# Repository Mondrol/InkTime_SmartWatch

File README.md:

# INK TIME SMARTWATCH

Un smartwatch bazat pe arhitectura **nRF52840**, echipat cu un ecran **e-Paper** pentru consum ultra-redus de energie și un sistem de alertă haptică.

---

## Cuprins

1. [Diagrama Bloc](#diagrama-bloc)
2. [Descrierea Funcționalității Hardware](#descrierea-funcționalității-hardware)
3. [Bill of Materials (BOM)](#bill-of-materials-bom)
4. [Configurația Pinilor nRF52840](#configurația-pinilor-nrf52840)

---

## Diagrama Bloc

```
┌─────────────────────────────────────────────────────────────┐
│                        POWER SUPPLY                         │
│                                                             │
│  Li-Po Battery (3.7V)                                       │
│       │                                                     │
│       ▼                                                     │
│  BQ25180 (Charger IC)  ◄──── USB Type-C                     │
│       │                                                     │
│       ▼                                                     │
│  RT6160A (Buck-Boost)  ──► 3.3V stable output              │
│       │                                                     │
│  MAX17048 (Fuel Gauge) ──► I2C ──► nRF52840                 │
└─────────────────────────────────────────────────────────────┘

┌─────────────────────────────────────────────────────────────┐
│                     PROCESSING UNIT                         │
│                                                             │
│              nRF52840 (ARM Cortex-M4F)                      │
│         ┌──────────────┴──────────────┐                     │
│         │                            │                      │
│       SPI bus                     I2C bus                   │
│         │                            │                      │
│   e-Paper Display              ┌─────┴──────┐               │
│   (1.54")                      │            │               │
│                            BMA423      DRV2605L              │
│                          (Accel.)    (Haptic Driver)         │
└─────────────────────────────────────────────────────────────┘
```

---

## Descrierea Funcționalității Hardware

Sistemul este construit în jurul SoC-ului **nRF52840**, optimizat pentru un consum ultra-scăzut de energie și securitate hardware.

### Microcontroller — nRF52840

Procesor ARM Cortex-M4F cu unitate de criptare hardware CryptoCell-310. Gestionează stack-ul **Bluetooth Low Energy (BLE)** și coordonează toate perifericele. Rulează la 64 MHz, dar stă majoritatea timpului în modul **System ON Sleep** (~3 µA).

### Sistemul de Alimentare (Power Tree)

| Componentă | Rol |
|---|---|
| **BQ25180** | IC de încărcare cu Power Path — permite încărcarea bateriei LiPo și alimentarea simultană a sistemului via USB Type-C |
| **MAX17048** | Fuel Gauge — măsoară precis starea de încărcare (SoC) și tensiunea bateriei, comunicând prin I2C |
| **RT6160A** | Regulator Buck-Boost — asigură o tensiune stabilă de 3.3V indiferent de nivelul de descărcare al bateriei |

### Afișaj e-Paper (1.54")

Display de tip *Electronic Ink* care consumă curent **doar la refresh**. Include un circuit de protecție cu un PFET (DMG2305UX) pentru a opri complet alimentarea ecranului în standby, eliminând scurgerile de curent. Comunică cu MCU prin **SPI** (interfață de mare viteză).

### Senzor de Mișcare — BMA423

Accelerometru triaxial de mică putere (12-bit, 3 axe). Utilizat pentru:
- **Pedometru** (numărarea pașilor)
- **Detectarea gesturilor** — ex: *tilt-to-wake* (ridicarea mâinii aprinde ecranul)

### Driver Haptic — DRV2605L

Controlează motorul de vibrații (ERM/LRA) folosind librării de efecte pre-programate pentru feedback tactil. Comunică prin **I2C**.

### Cristale de Referință

**Cristal 32 MHz (X1)** — esențial pentru funcționarea blocului radio (Bluetooth). Oferă referința de înaltă frecvență necesară stabilității semnalului RF și procesării rapide a datelor.

**Cristal 32.768 kHz (X2)** — componentă critică pentru optimizarea consumului. Permite funcționarea ceasului de timp real (RTC) în modurile de **Deep Sleep**, menținând precizia timpului cu un consum infim de energie, fără a fi nevoie de oscilatorul intern RC (mai puțin precis și mai consumator).

### Antena 2.4 GHz

Antenă de tip **SMD ceramic** (Johanson 2450AT18B100E) pentru frecvența de 2.4 GHz (BLE). A fost respectată o zonă de *keep-out* (fără cupru) pe toate straturile sub antenă pentru a preveni atenuarea semnalului.

### Interfețe de Comunicație

| Interfață | Periferice conectate |
|---|---|
| **I2C** | BMA423, DRV2605L, BQ25180, MAX17048 |
| **SPI** | Display e-Paper (interfață de mare viteză) |
| **GPIO cu întreruperi** | Butoane UP / ENTER / DOWN |
| **SWD** | Programare și debugging via Tag-Connect (J2) |

### Consumul de Energie

Bateria de **250 mAh** susține o autonomie estimată de **30–45 zile**, datorită:
- Ecranului e-Paper care nu consumă energie între actualizări
- Senzorilor configurați pe modul de consum minim cu întreruperi
- nRF52840 în System ON Sleep (~3 µA) marea majoritate a timpului

---

## Bill of Materials (BOM)

| Componentă | Descriere | Qty | Ref. Designator | Producător |
|---|---|:---:|---|---|
| **nRF52840** | MCU ARM Cortex-M4F + BLE 5.0 | 1 | U1 | Nordic Semiconductor |
| **BQ25180YBGR** | IC Încărcare Baterie Li-Po/Li-Ion | 1 | IC1 | Texas Instruments |
| **MAX17048G+T10** | Fuel Gauge 1-Cell cu ModelGauge | 1 | U2 | Analog Devices (Maxim) |
| **RT6160AWSC** | Regulator Buck-Boost DC-DC I2C | 1 | IC9 | Richtek |
| **DRV2605YZFR** | Driver Haptic ERM/LRA | 1 | IC2 | Texas Instruments |
| **BMA423** | Accelerometru Triaxial Low-g 12-bit | 1 | IC3 | Bosch Sensortec |
| **2450AT18B100E** | Antenă SMD 2.45 GHz (BLE) | 1 | ANT1 | Johanson Technology |
| **KH-TYPE-C-16P** | Conector USB Type-C 16 pini | 1 | J4 | Kinghelm |
| **503480-2400** | Conector FPC 24 pini, pitch 0.5mm (Display) | 1 | J1 | Molex |
| **TC2030-IDC** | Conector programare Tag-Connect 6 pini | 1 | J2 | Tag-Connect |
| **USBLC6-2SC6Y** | Diodă TVS Protecție ESD (USB) | 1 | D3 | STMicroelectronics |
| **MBR0530** | Diodă Schottky 30V / 0.5A | 3 | D2, D4, D5 | ON Semiconductor |
| **DMG2305UX-7** | MOSFET P-Channel 20V / 4.2A (e-Paper power switch) | 1 | Q1 | Diodes Inc. |
| **SI1308EDL-T1-GE3** | MOSFET N-Channel 30V / 1.5A | 1 | Q3 | Vishay Siliconix |
| **EVP-AKE31A** | Butoane Tactile SMD (Navigare) | 3 | SW_UP, SW_DN, SW_ENT | Panasonic |
| **744043680** | Inductor / Bobină 68 µH | 1 | L5 | Würth Elektronik |
| **FTC252012SR47MBCA** | Inductor SMD 0.47 µH | 1 | L7 | TDK |
| **Cristal 32 MHz** | Referință RF pentru bloc radio BLE | 1 | X1 | — |
| **Cristal 32.768 kHz** | Referință RTC pentru Deep Sleep | 1 | X2 | — |
| **Condensatori / Rezistențe** | Pasive SMD (0201, 0402) | ~60 | C*, R* | — |
| **Test Pads** | Puncte de test (3.3V, GND, SWD, I2C etc.) | 14 | TP_* | — |

---

## Configurația Pinilor nRF52840

### Interfața Ecranului e-Paper (SPI)

| Semnal | Pin nRF52 | Direcție | Descriere |
|---|---|---|---|
| EPD_SCK | P0.28 | Output | Clock SPI pentru refresh ecran |
| EPD_MOSI | P0.29 | Output | Date imagine (frame buffer) |
| EPD_CS | P0.30 | Output | Chip Select — activează comunicația cu display-ul |
| EPD_DC | P0.31 | Output | Data/Command — diferențiază comenzile de datele de imagine |
| EPD_BUSY | P0.04 | Input | Semnal activ cât timp ecranul procesează un refresh |
| EPD_PWR | P0.13 | Output | Enable alimentare ecran — dezactivat complet în standby |

### Magistrala Senzorilor (I2C)

Toți senzorii (BMA423, MAX17048, DRV2605L, BQ25180) împart aceeași magistrală I2C.

| Semnal | Pin nRF52 | Descriere |
|---|---|---|
| I2C_SDA | P0.26 | Linie de date (partajată între toți senzorii) |
| I2C_SCL | P0.27 | Linie de clock |

### Butoane de Navigare

Pini configurați cu pull-up intern și capabili de **wake-up din Deep Sleep** prin întrerupere hardware.

| Buton | Pin nRF52 | Funcție |
|---|---|---|
| UP | P1.00 | Navigare meniu — sus |
| DOWN | P1.01 | Navigare meniu — jos |
| ENTER | P1.02 | Selecție / Confirmare |

### Alte Conexiuni Importante

| Semnal | Pin nRF52 | Descriere |
|---|---|---|
| SHAKER_EN | P0.02 | PWM / Enable pentru driver haptic DRV2605 |
| GAUGE_INT | P1.15 | Întrerupere de la MAX17048 la nivel critic de baterie |
| LED_1 | P0.13 | LED de stare pentru notificări vizuale |
| LED_2 | P0.14 | LED de stare secundar |
| SWDIO | — | Programare și debug via Tag-Connect J2 |
| SWDCLK | — | Clock SWD pentru J-Link |

---

## Imagini PCB

| PCB 3D View | Exploded View | Final View |
|---|---|---|
| `./Images/PCB_3D.png` | `./Images/exploded_view.png` | `./Images/final_view.png` |

---

*INK TIME SMARTWATCH — Hardware Design Documentation*

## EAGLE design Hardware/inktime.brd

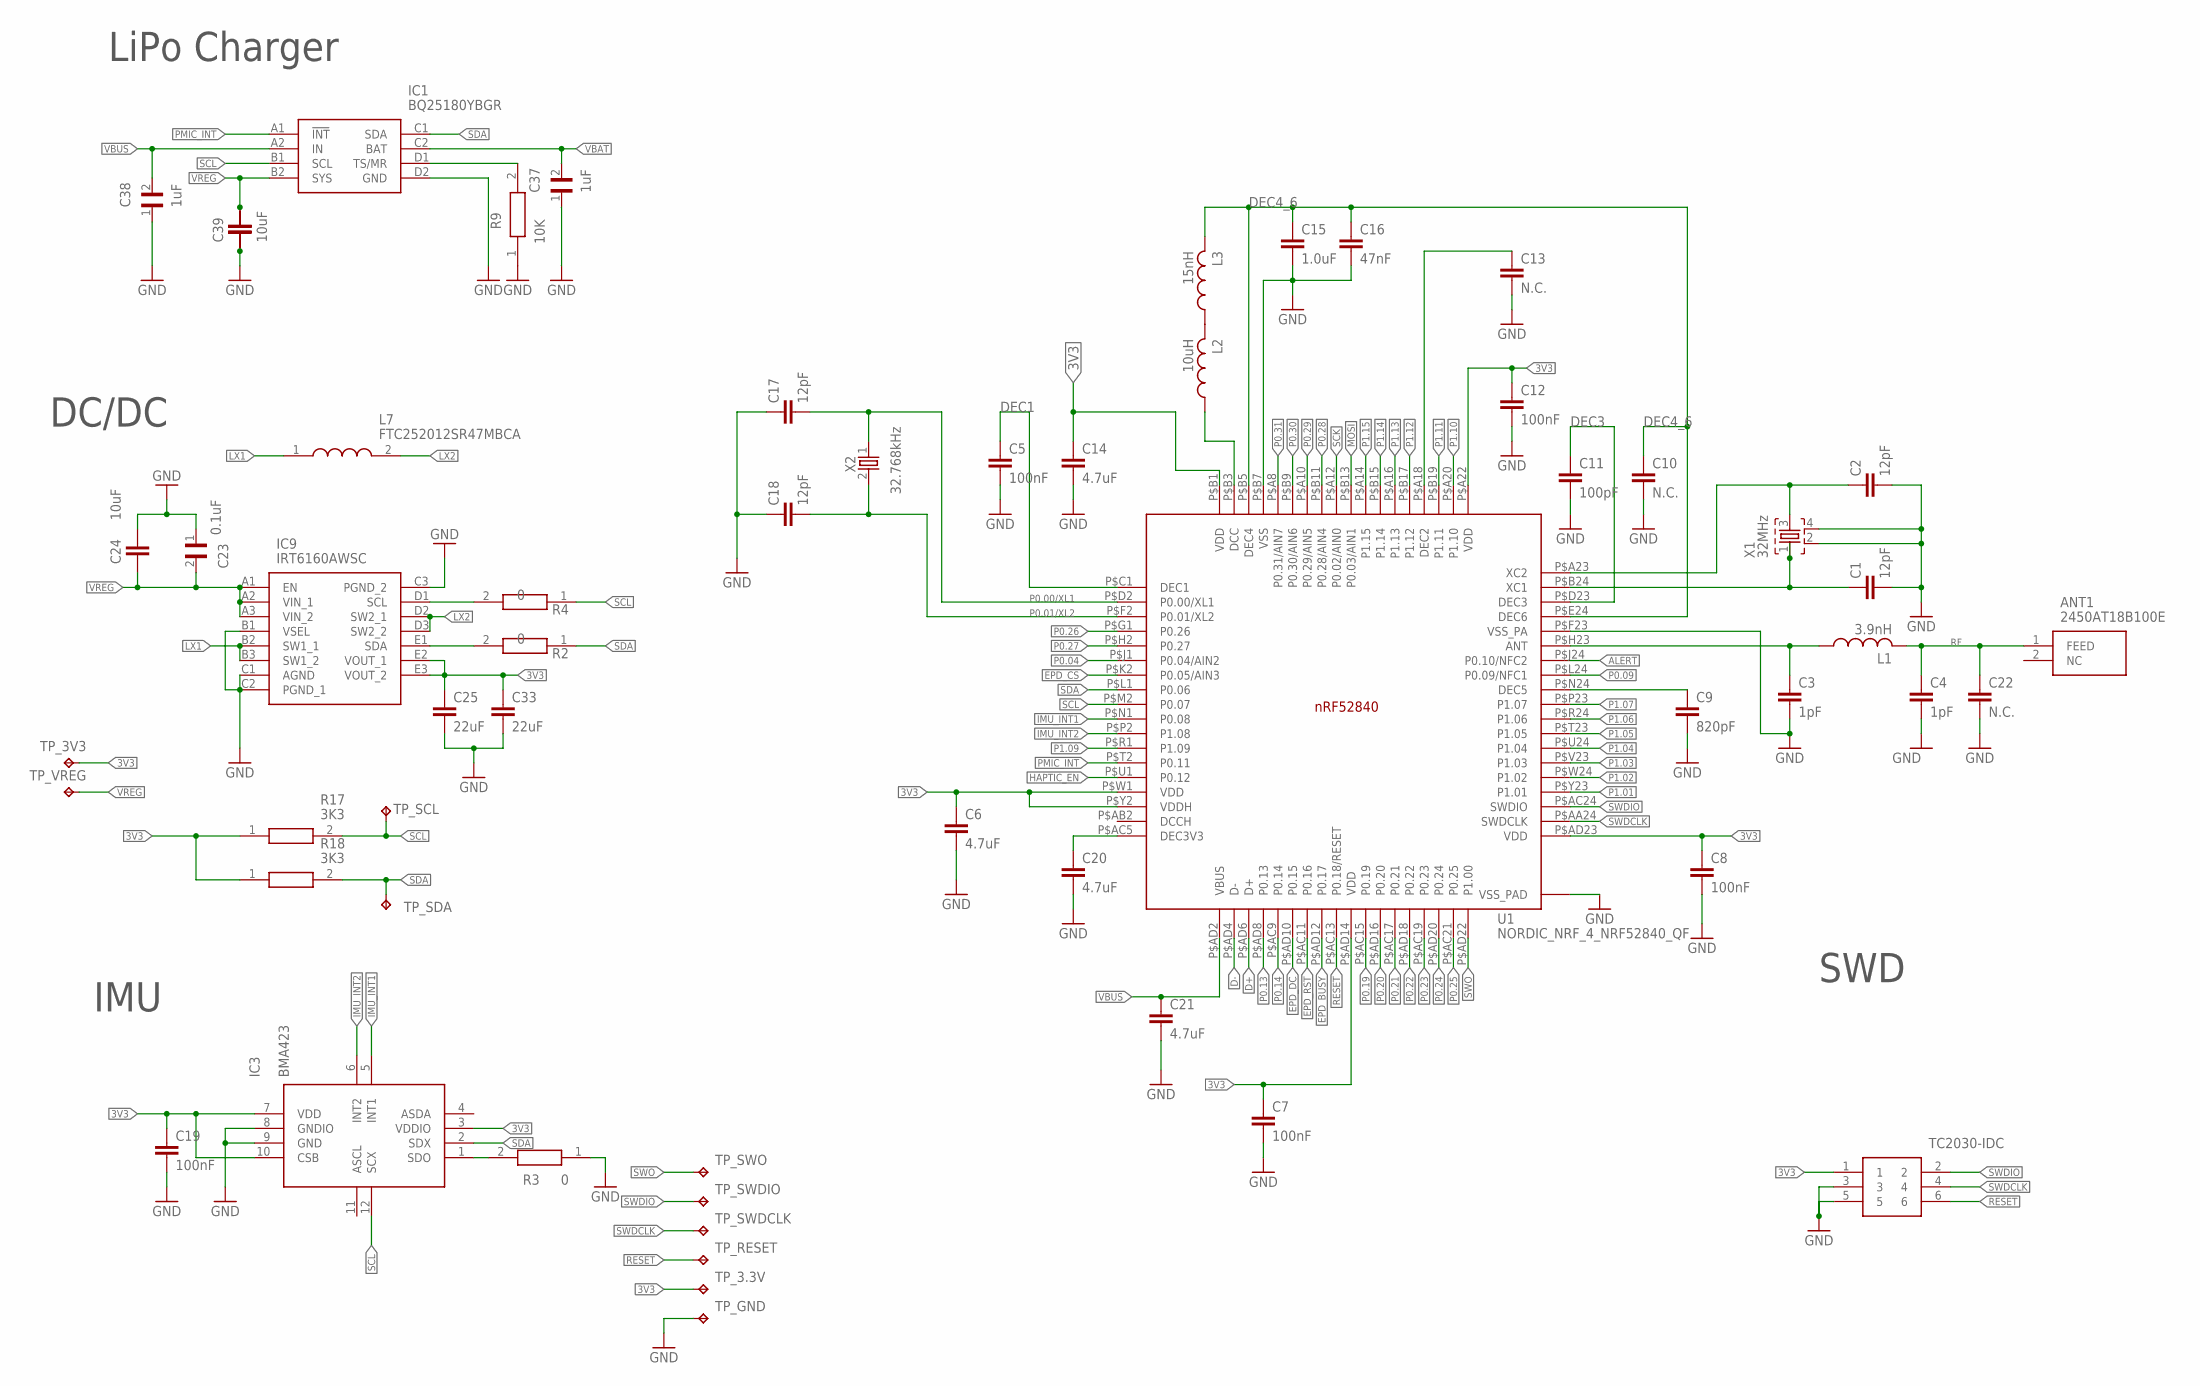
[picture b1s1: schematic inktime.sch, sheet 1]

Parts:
ANT1: 2450AT18B100E; 2450AT18B100E_ANTC3216X140N
C1, C2, C17, C18: 12pF; NORDIC_NRF_3_RESC0201_L
C3, C4: 1pF; NORDIC_NRF_3_RESC0201_L
C5, C7, C8, C12, C19: 100nF; NORDIC_NRF_3_RESC0201_L
C6, C14, C20, C21: 4.7uF; NORDIC_NRF_3_RESC0402_L
C9: 820pF; NORDIC_NRF_3_RESC0201_L
C10, C13, C22: N.C.; NORDIC_NRF_3_RESC0201_L
C11: 100pF; NORDIC_NRF_3_RESC0201_L
C15: 1.0uF; NORDIC_NRF_3_RESC0402_L
C16: 47nF; NORDIC_NRF_3_RESC0201_L
C23: 0.1uF; GRM011R60J152KE01L_2_CAPC0201X13N
C24, C39: 10uF; NORDIC_NRF_3_RESC0402_L
C25, C33: 22uF; NORDIC_NRF_3_RESC0402_L
C37, C38: 1uF; GRM011R60J152KE01L_2_CAPC0201X13N
IC1: BQ25180YBGR; BQ25180YBGR_BGA8C40P2X4_100X155X50
IC3: BMA423; BMA423_BMA423
IC9: IRT6160AWSC; RT6160AWSC_BGA15C40P3X5_140X230X60
J2: TC2030-IDC; TC2030-IDC_TC2030IDC
L1: 3.9nH; NORDIC_NRF_2_RESC0402_L
L2: 10uH; NORDIC_NRF_2_RESC0402_L
L3: 15nH; NORDIC_NRF_2_RESC0402_L
L7: FTC252012SR47MBCA; MLP2016SR47MT0S1_INDC2016X100N
R2, R4: 0; ERA-1AEB3401C_0201
R3: 0; CPF0201D7K68C1_0201
R9: 10K; ERA-1AEB3401C_0201
R17, R18: 3K3; CPF0201D7K68C1_0201
TP_3.3V, TP_3V3: HECTOR_WATCH_1_TPTP20R; HECTOR_WATCH_1_TP20R
TP_GND: HECTOR_WATCH_1_TPTP20R; HECTOR_WATCH_1_TP20R
TP_RESET: HECTOR_WATCH_1_TPTP20R; HECTOR_WATCH_1_TP20R
TP_SCL: HECTOR_WATCH_1_TPTP20R; HECTOR_WATCH_1_TP20R
TP_SDA: HECTOR_WATCH_1_TPTP20R; HECTOR_WATCH_1_TP20R
TP_SWDCLK: HECTOR_WATCH_1_TPTP20R; HECTOR_WATCH_1_TP20R
TP_SWDIO: HECTOR_WATCH_1_TPTP20R; HECTOR_WATCH_1_TP20R
TP_SWO: HECTOR_WATCH_1_TPTP20R; HECTOR_WATCH_1_TP20R
TP_VREG: HECTOR_WATCH_1_TPTP20R; HECTOR_WATCH_1_TP20R
U1: NORDIC_NRF_4_NRF52840_QF; NORDIC_NRF_4_AQFN50P700X700X85_HS-74N
U$3: NORDIC_NRF_3_CAPACITOR_0402_L; NORDIC_NRF_3_RESC0402_L
X1: 32MHz; NORDIC_NRF_BT-XTAL_2016_N
X2: 32.768kHz; NORDIC_NRF_1_XTAL_3215_N

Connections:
3V3: C6.1, C7.1, C8.1, C12.1, C14.1, C19.1, C25.1, C33.1, IC3.3 (VDDIO), IC3.7 (VDD), IC3.10 (CSB), IC9.E2 (VOUT_1), IC9.E3 (VOUT_2), J2.1, R17.1, R18.1, TP_3.3V.TP, TP_3V3.TP, U1.P$A22 (VDD), U1.P$AD14 (VDD), U1.P$AD23 (VDD), U1.P$B1 (VDD), U1.P$W1 (VDD), U1.P$Y2 (VDDH); also elsewhere on the board
ALERT: U1.P$J24 (P0.10/NFC2); also elsewhere on the board
D+: U1.P$AD6 (D+); also elsewhere on the board
D-: U1.P$AD4 (D-); also elsewhere on the board
DEC1: C5.1, U1.P$C1 (DEC1)
DEC3: C11.1, U1.P$D23 (DEC3)
DEC4_6: C10.1, C15.1, C16.1, L3.2, U1.P$B5 (DEC4), U1.P$E24 (DEC6)
EPD_BUSY: U1.P$AD12 (P0.17); also elsewhere on the board
EPD_CS: U1.P$K2 (P0.05/AIN3); also elsewhere on the board
EPD_DC: U1.P$AD10 (P0.15); also elsewhere on the board
EPD_RST: U1.P$AC11 (P0.16); also elsewhere on the board
GND: C1.2, C2.2, C3.2, C4.2, C5.2, C6.2, C7.2, C8.2, C9.2, C10.2, C11.2, C12.2, C13.2, C14.2, C15.2, C16.2, C17.1, C18.1, C19.2, C20.2, C21.2, C22.2, C23.1, C24.1, C25.2, C33.2, C37.1, C38.1, C39.2, IC1.D2 (GND), IC3.8 (GNDIO), IC3.9 (GND), IC9.B1 (VSEL), IC9.C1 (AGND), IC9.C2 (PGND_1), IC9.C3 (PGND_2), J2.3, J2.5, R3.1, R9.1, TP_GND.TP, U1.P$74 (VSS_PAD), U1.P$75 (VSS_PAD), U1.P$76 (VSS_PAD), U1.P$77 (VSS_PAD), U1.P$78 (VSS_PAD), U1.P$79 (VSS_PAD), U1.P$80 (VSS_PAD), U1.P$81 (VSS_PAD), U1.P$82 (VSS_PAD), U1.P$83 (VSS_PAD), U1.P$84 (VSS_PAD), U1.P$85 (VSS_PAD), U1.P$86 (VSS_PAD), U1.P$87 (VSS_PAD), U1.P$88 (VSS_PAD), U1.P$89 (VSS_PAD), U1.P$90 (VSS_PAD), U1.P$B7 (VSS), U1.P$F23 (VSS_PA), U$3.2, X1.2, X1.4; also elsewhere on the board
HAPTIC_EN: U1.P$U1 (P0.12); also elsewhere on the board
IMU_INT1: IC3.5 (INT1), U1.P$N1 (P0.08)
IMU_INT2: IC3.6 (INT2), U1.P$P2 (P1.08)
LX1: IC9.B2 (SW1_1), IC9.B3 (SW1_2), L7.1
LX2: IC9.D2 (SW2_1), IC9.D3 (SW2_2), L7.2
MOSI: U1.P$B13 (P0.03/AIN1); also elsewhere on the board
unnamed: C2.1, U1.P$A23 (XC2), X1.3
unnamed: C1.1, U1.P$B24 (XC1), X1.1
unnamed: L2.2, L3.1
unnamed: L2.1, U1.P$B3 (DCC)
unnamed: IC3.1 (SDO), R3.2
unnamed: C3.1, L1.1, U1.P$H23 (ANT)
unnamed: C13.1, U1.P$A18 (DEC2)
unnamed: C9.1, U1.P$N24 (DEC5)
unnamed: C20.1, U1.P$AC5 (DEC3V3)
unnamed: IC9.D1 (SCL), R4.2
unnamed: IC1.D1 (TS/MR), R9.2
unnamed: IC9.E1 (SDA), R2.2
P0.00/XL1: C17.2, U1.P$D2 (P0.00/XL1), X2.1
P0.01/XL2: C18.2, U1.P$F2 (P0.01/XL2), X2.2
P0.04: U1.P$J1 (P0.04/AIN2)
P0.09: U1.P$L24 (P0.09/NFC1)
P0.13: U1.P$AD8 (P0.13); also elsewhere on the board
P0.14: U1.P$AC9 (P0.14); also elsewhere on the board
P0.19: U1.P$AC15 (P0.19)
P0.20: U1.P$AD16 (P0.20)
P0.21: U1.P$AC17 (P0.21)
P0.22: U1.P$AD18 (P0.22)
P0.23: U1.P$AC19 (P0.23)
P0.24: U1.P$AD20 (P0.24)
P0.25: U1.P$AC21 (P0.25)
P0.26: U1.P$G1 (P0.26)
P0.27: U1.P$H2 (P0.27)
P0.28: U1.P$B11 (P0.28/AIN4)
P0.29: U1.P$A10 (P0.29/AIN5)
P0.30: U1.P$B9 (P0.30/AIN6)
P0.31: U1.P$A8 (P0.31/AIN7)
P1.01: U1.P$Y23 (P1.01); also elsewhere on the board
P1.02: U1.P$W24 (P1.02); also elsewhere on the board
P1.03: U1.P$V23 (P1.03)
P1.04: U1.P$U24 (P1.04)
P1.05: U1.P$T23 (P1.05)
P1.06: U1.P$R24 (P1.06)
P1.07: U1.P$P23 (P1.07)
P1.09: U1.P$R1 (P1.09)
P1.10: U1.P$A20 (P1.10)
P1.11: U1.P$B19 (P1.11)
P1.12: U1.P$B17 (P1.12)
P1.13: U1.P$A16 (P1.13)
P1.14: U1.P$B15 (P1.14)
P1.15: U1.P$A14 (P1.15)
PMIC_INT: IC1.A1 (!INT), U1.P$T2 (P0.11)
RESET: J2.6, TP_RESET.TP, U1.P$AC13 (P0.18/RESET)
RF: ANT1.1 (FEED), C4.1, C22.1, L1.2
SCK: U1.P$A12 (P0.02/AIN0); also elsewhere on the board
SCL: IC1.B1 (SCL), IC3.12 (SCX), R4.1, R17.2, TP_SCL.TP, U1.P$M2 (P0.07); also elsewhere on the board
SDA: IC1.C1 (SDA), IC3.2 (SDX), R2.1, R18.2, TP_SDA.TP, U1.P$L1 (P0.06); also elsewhere on the board
SWDCLK: J2.4, TP_SWDCLK.TP, U1.P$AA24 (SWDCLK)
SWDIO: J2.2, TP_SWDIO.TP, U1.P$AC24 (SWDIO)
SWO: TP_SWO.TP, U1.P$AD22 (P1.00)
VBAT: C37.2, IC1.C2 (BAT); also elsewhere on the board
VBUS: C21.1, C38.2, IC1.A2 (IN), U1.P$AD2 (VBUS); also elsewhere on the board
VREG: C23.2, C24.2, C39.1, IC1.B2 (SYS), IC9.A1 (EN), IC9.A2 (VIN_1), IC9.A3 (VIN_2), TP_VREG.TP, U$3.1

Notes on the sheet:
LiPo Charger
DC/DC
IMU
SWD

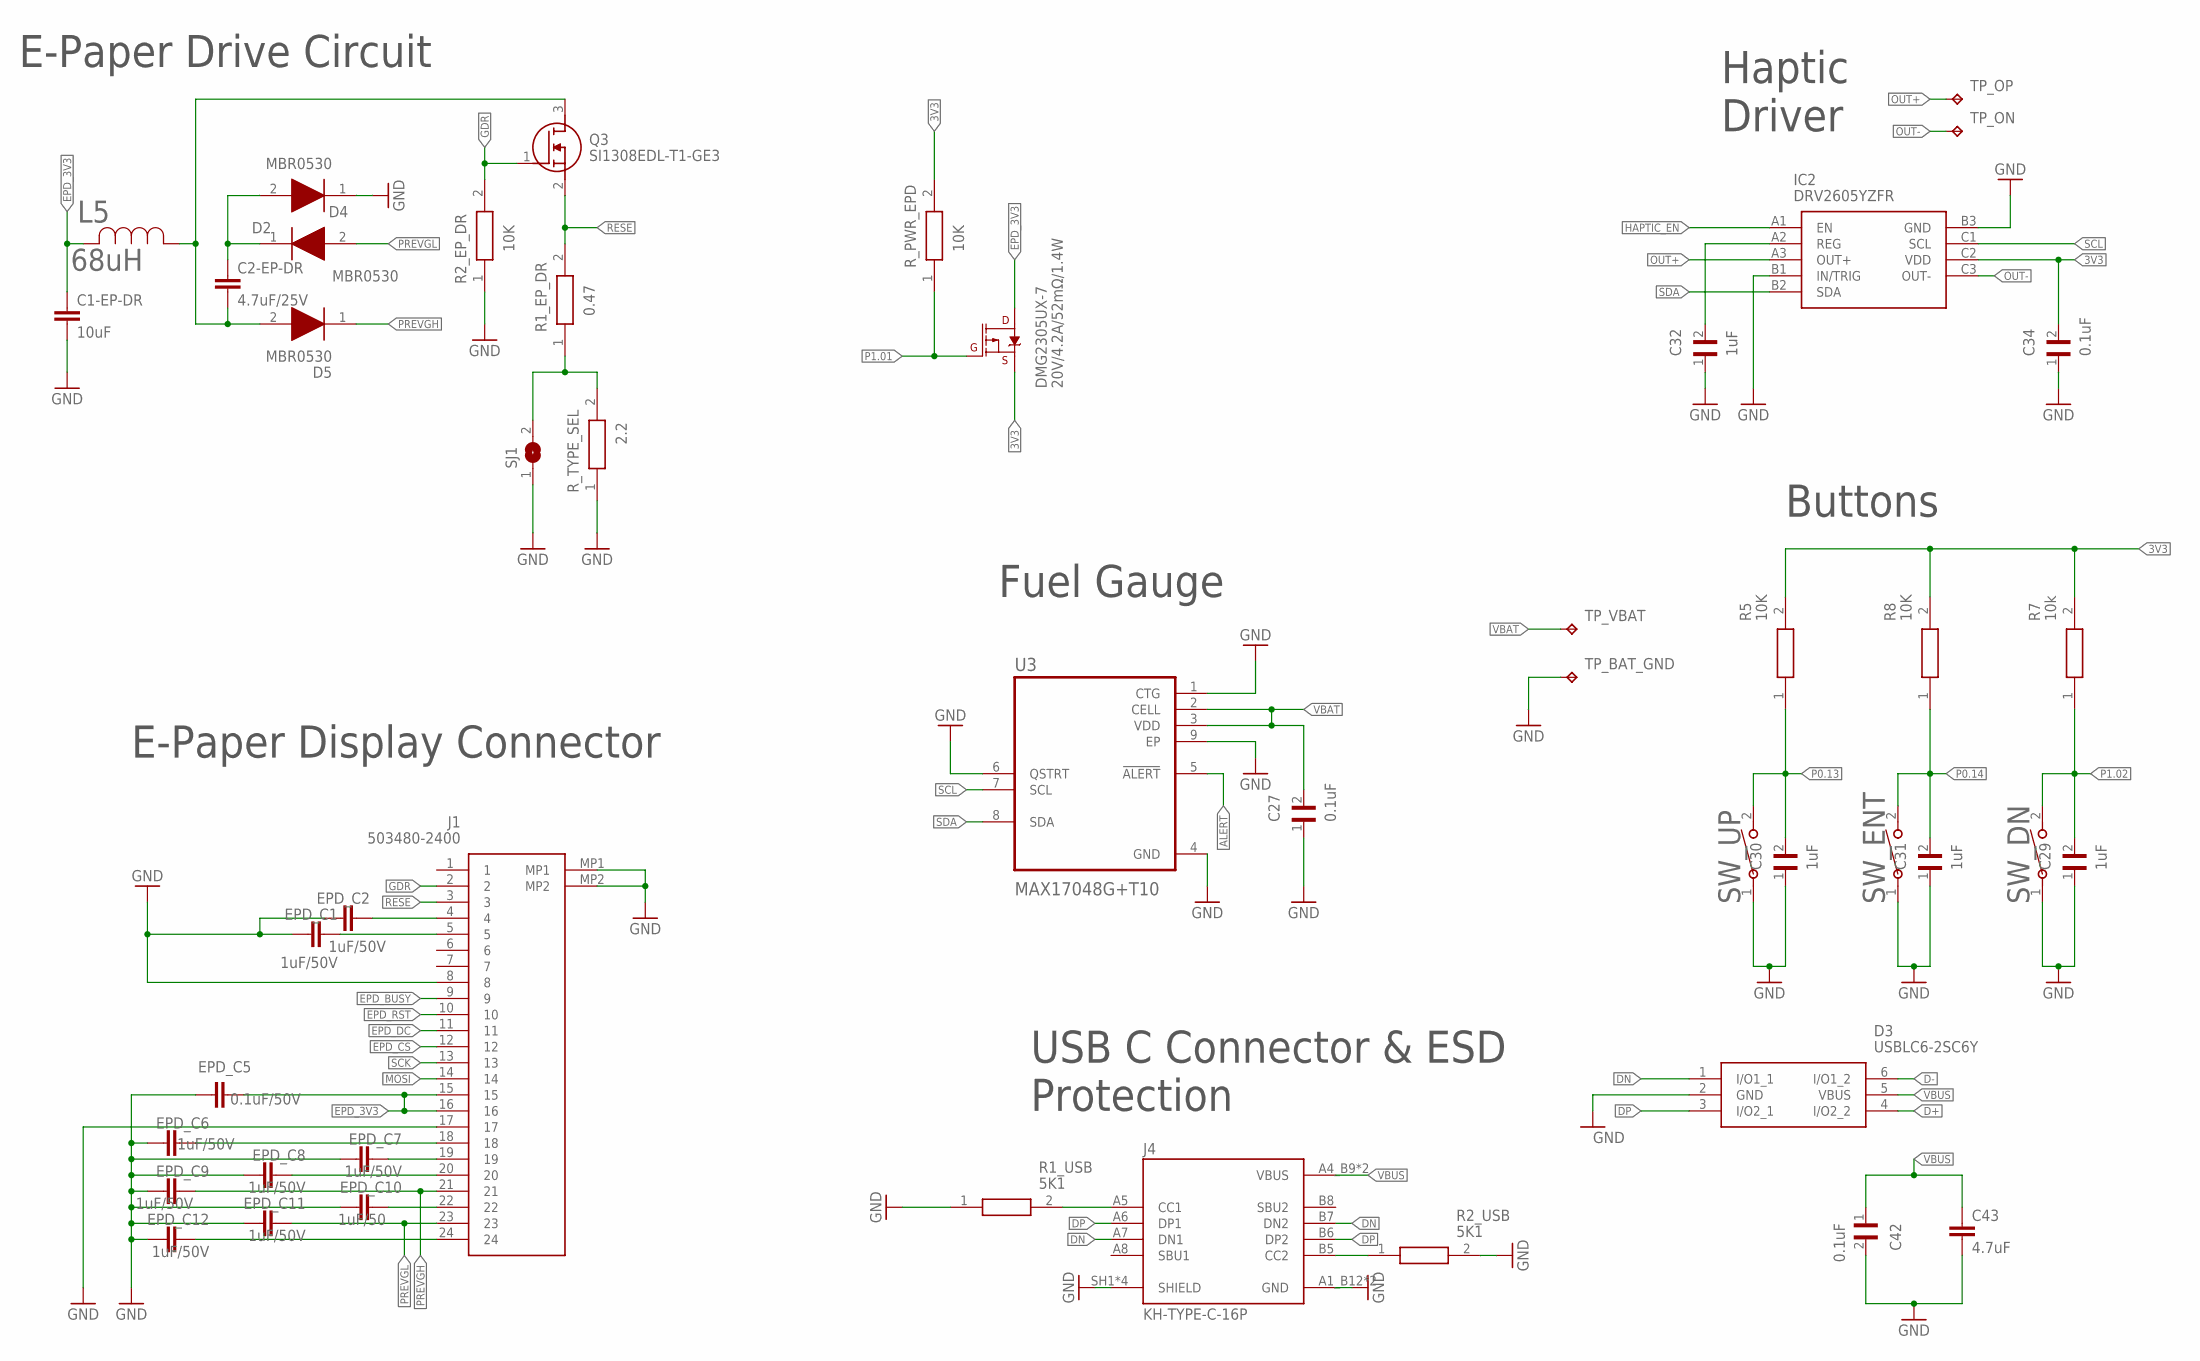
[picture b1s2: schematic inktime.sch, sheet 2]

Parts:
C1-EP-DR: 10uF; NORDIC_NRF_3_RESC0402_L
C2-EP-DR: 4.7uF/25V; NORDIC_NRF_3_RESC0402_L
C27, C34, C42: 0.1uF; GRM011R60J152KE01L_2_CAPC0201X13N
C29, C30, C31, C32: 1uF; GRM011R60J152KE01L_2_CAPC0201X13N
C43: 4.7uF; NORDIC_NRF_3_RESC0402_L
D2, D4, D5: MBR0530; ESP32_C6_LIBRARY_5_SOD3716X135N
D3: USBLC6-2SC6Y; ESP32_C6_LIBRARY_3_SOT95P280X145-6N
DMG2305UX-7: 20V/4.2A/52mΩ/1.4W; ESP32_C6_LIBRARY_4_ESP32_C6_LIBRARY_4_ESP32_C6_LIBRARY_4_ES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
EPD_C1, EPD_C2, EPD_C6, EPD_C7, EPD_C8, EPD_C9, EPD_C11, EPD_C12: 1uF/50V; NORDIC_NRF_3_RESC0402_L
EPD_C5: 0.1uF/50V; NORDIC_NRF_3_RESC0201_L
EPD_C10: 1uF/50; NORDIC_NRF_3_RESC0402_L
IC2: DRV2605YZFR; DRV2605YZFR_BGA9C50P3X3_144X144X62
J1: 503480-2400; 503480-2400_5034802400
J4: KH-TYPE-C-16P; KH-TYPE-C-16P_KINGHELM_KH-TYPE-C-16P
L5: 68uH; ESP32_C6_LIBRARY_2_IND_4828-WE-TPC_WRE
Q3: SI1308EDL-T1-GE3; ESP32_C6_LIBRARY_6_SOT65P210X110-3N
R1_EP_DR: 0.47; ERA-1AEB3401C_0201
R1_USB, R2_USB: 5K1; ERA-1AEB3401C_0201
R2_EP_DR, R5, R8: 10K; ERA-1AEB3401C_0201
R7: 10k; ERA-1AEB3401C_0201
R_PWR_EPD: 10K; ERA-1AEB3401C_0201
R_TYPE_SEL: 2.2; ERA-1AEB3401C_0201
SJ1: ESP32_C6_LIBRARY_7_JUMPER_SJ
SW_DN: 2025-10-22_07-23-44_LIBRARY_EVP-AKE31ASW_EVP-AKE3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; 2025-10-22_07-23-44_LIBRARY_SW_EVP-AKE31A_PAN
SW_ENT: 2025-10-22_07-23-44_LIBRARY_EVP-AKE31ASW_EVP-AKE3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; 2025-10-22_07-23-44_LIBRARY_SW_EVP-AKE31A_PAN
SW_UP: 2025-10-22_07-23-44_LIBRARY_EVP-AKE31ASW_EVP-AKE3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; 2025-10-22_07-23-44_LIBRARY_SW_EVP-AKE31A_PAN
TP_BAT_GND: HECTOR_WATCH_1_TPTP20R; HECTOR_WATCH_1_TP20R
TP_ON: HECTOR_WATCH_1_TPTP20R; HECTOR_WATCH_1_TP20R
TP_OP: HECTOR_WATCH_1_TPTP20R; HECTOR_WATCH_1_TP20R
TP_VBAT: HECTOR_WATCH_1_TPTP20R; HECTOR_WATCH_1_TP20R
U3: MAX17048G+T10; ESP32_C6_LIBRARY_SON50P200X200X80-9N

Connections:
3V3: C34.2, DMG2305UX-7.2 (S), IC2.C2 (VDD), R5.2, R7.2, R8.2, R_PWR_EPD.2; also elsewhere on the board
ALERT: U3.5 (!ALERT); also elsewhere on the board
D+: D3.4 (I/O2_2); also elsewhere on the board
D-: D3.6 (I/O1_2); also elsewhere on the board
DN: D3.1 (I/O1_1), J4.A7 (DN1), J4.B7 (DN2)
DP: D3.3 (I/O2_1), J4.A6 (DP1), J4.B6 (DP2)
EPD_3V3: C1-EP-DR.1, DMG2305UX-7.3 (D), EPD_C5.1, J1.15, J1.16, L5.2
EPD_BUSY: J1.9; also elsewhere on the board
EPD_CS: J1.12; also elsewhere on the board
EPD_DC: J1.11; also elsewhere on the board
EPD_RST: J1.10; also elsewhere on the board
GDR: J1.2, Q3.1 (G), R2_EP_DR.2
GND: C1-EP-DR.2, C27.1, C29.1, C30.1, C31.1, C32.1, C34.1, C42.2, C43.2, D3.2 (GND), D4.1 (K), EPD_C1.1, EPD_C2.1, EPD_C5.2, EPD_C6.1, EPD_C7.1, EPD_C8.1, EPD_C9.1, EPD_C10.1, EPD_C11.1, EPD_C12.1, IC2.B1 (IN/TRIG), IC2.B3 (GND), J1.8, J1.17, J1.MP1, J1.MP2, J4.A1_B12 (GND), J4.A12_B1 (GND), J4.SH1 (SHIELD), J4.SH2 (SHIELD), J4.SH3 (SHIELD), J4.SH4 (SHIELD), R1_USB.1, R2_EP_DR.1, R2_USB.2, R_TYPE_SEL.1, SJ1.1, SW_DN.1, SW_ENT.1, SW_UP.1, TP_BAT_GND.TP, U3.1 (CTG), U3.4 (GND), U3.6 (QSTRT), U3.9 (EP); also elsewhere on the board
HAPTIC_EN: IC2.A1 (EN); also elsewhere on the board
MOSI: J1.14; also elsewhere on the board
unnamed: C32.2, IC2.A2 (REG)
unnamed: C2-EP-DR.2, D5.2 (A), L5.1, Q3.3 (D)
unnamed: C2-EP-DR.1, D2.1 (K), D4.2 (A)
unnamed: J4.B5 (CC2), R2_USB.1
unnamed: J4.A5 (CC1), R1_USB.2
unnamed: EPD_C2.2, J1.4
unnamed: EPD_C1.2, J1.5
unnamed: R1_EP_DR.1, R_TYPE_SEL.2, SJ1.2
unnamed: EPD_C6.2, J1.18
unnamed: EPD_C7.2, J1.19
unnamed: EPD_C8.2, J1.20
unnamed: EPD_C10.2, J1.22
unnamed: EPD_C12.2, J1.24
OUT+: IC2.A3 (OUT+), TP_OP.TP
OUT-: IC2.C3 (OUT-), TP_ON.TP
P0.13: C30.2, R5.1, SW_UP.2; also elsewhere on the board
P0.14: C31.2, R8.1, SW_ENT.2; also elsewhere on the board
P1.01: DMG2305UX-7.1 (G), R_PWR_EPD.1; also elsewhere on the board
P1.02: C29.2, R7.1, SW_DN.2; also elsewhere on the board
PREVGH: D5.1 (K), EPD_C9.2, J1.21
PREVGL: D2.2 (A), EPD_C11.2, J1.23
RESE: J1.3, Q3.2 (S), R1_EP_DR.2
SCK: J1.13; also elsewhere on the board
SCL: IC2.C1 (SCL), U3.7 (SCL); also elsewhere on the board
SDA: IC2.B2 (SDA), U3.8 (SDA); also elsewhere on the board
VBAT: C27.2, TP_VBAT.TP, U3.2 (CELL), U3.3 (VDD); also elsewhere on the board
VBUS: C42.1, C43.1, D3.5 (VBUS), J4.A4_B9 (VBUS), J4.A9_B4 (VBUS); also elsewhere on the board

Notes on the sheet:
E-Paper Drive Circuit
E-Paper Display Connector
Fuel Gauge
Haptic Driver
Buttons
USB C Connector & ESD Protection

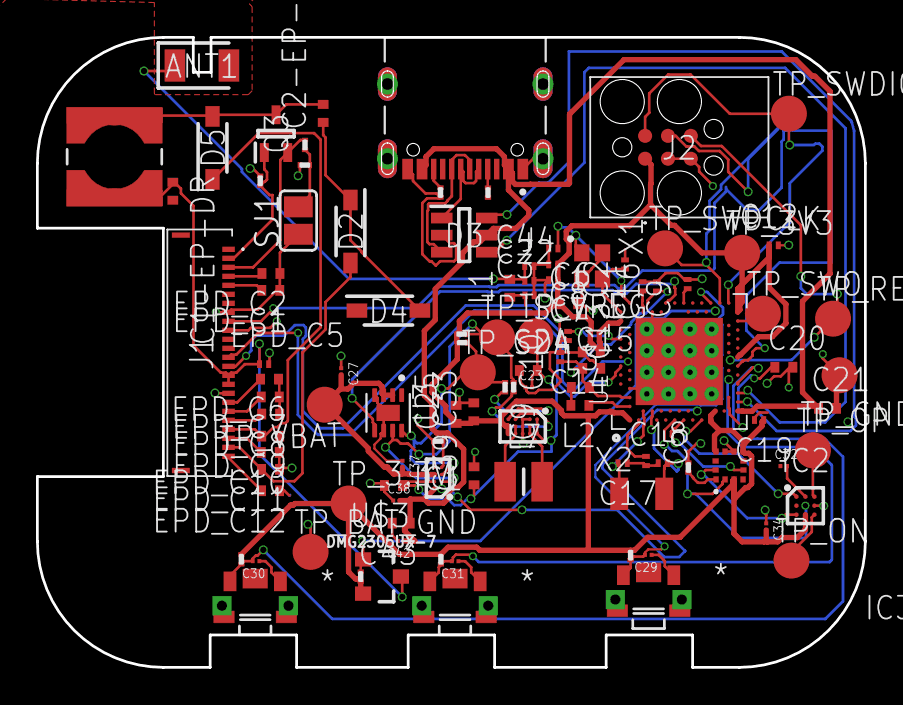
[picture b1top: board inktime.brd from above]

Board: 2 copper layers, 46.0 x 35.0 mm, 106 parts (0 on the bottom side), 70 nets.

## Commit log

2026-04-19 Delete Hardware/inktime.brd
    Sters pentru a il inlocui cu ultima varianta buna
2026-04-19 Delete Hardware/inktime.sch
    Sters pentru a il inlocui cu varianta buna
2026-04-19 Ultima varianta a folderului Hardware
2026-04-19 Am adaugat folderul Images
    Aici se regasesc poze cu: schematicul, PCB 2D si 3D si celelalte componente 3D bateria si displayul
2026-04-19 Delete Manufacturing directory
    L am sters pentru a face loc noului director cu fisierele corectate
2026-04-19 Am pus ultima varianta corecta a Manufacturing
2026-04-19 am adaugat si folderul Mechanical
    am adaugat numai o parte
2026-04-19 aici este ceasul complet
    l am pus zip pentru ca nu puteam sa pun fisiere peste 25mb
2026-04-20 Enhance README with hardware details and BOM
    Added detailed hardware functionality description, pin allocation, and a Bill of Materials for the InkTime SmartWatch project.
2026-04-20 Revise diagrams and components in README.md
    Updated the power supply and processing unit diagrams, and modified peripheral components in the README.
2026-04-20 Readme ul adaugat

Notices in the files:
parts and their libraries:
COPYRIGHT: Copyright (C) 2024 Ultra Librarian. All rights reserved.
COPYRIGHT: Copyright (C) 2025 Ultra Librarian. All rights reserved.
